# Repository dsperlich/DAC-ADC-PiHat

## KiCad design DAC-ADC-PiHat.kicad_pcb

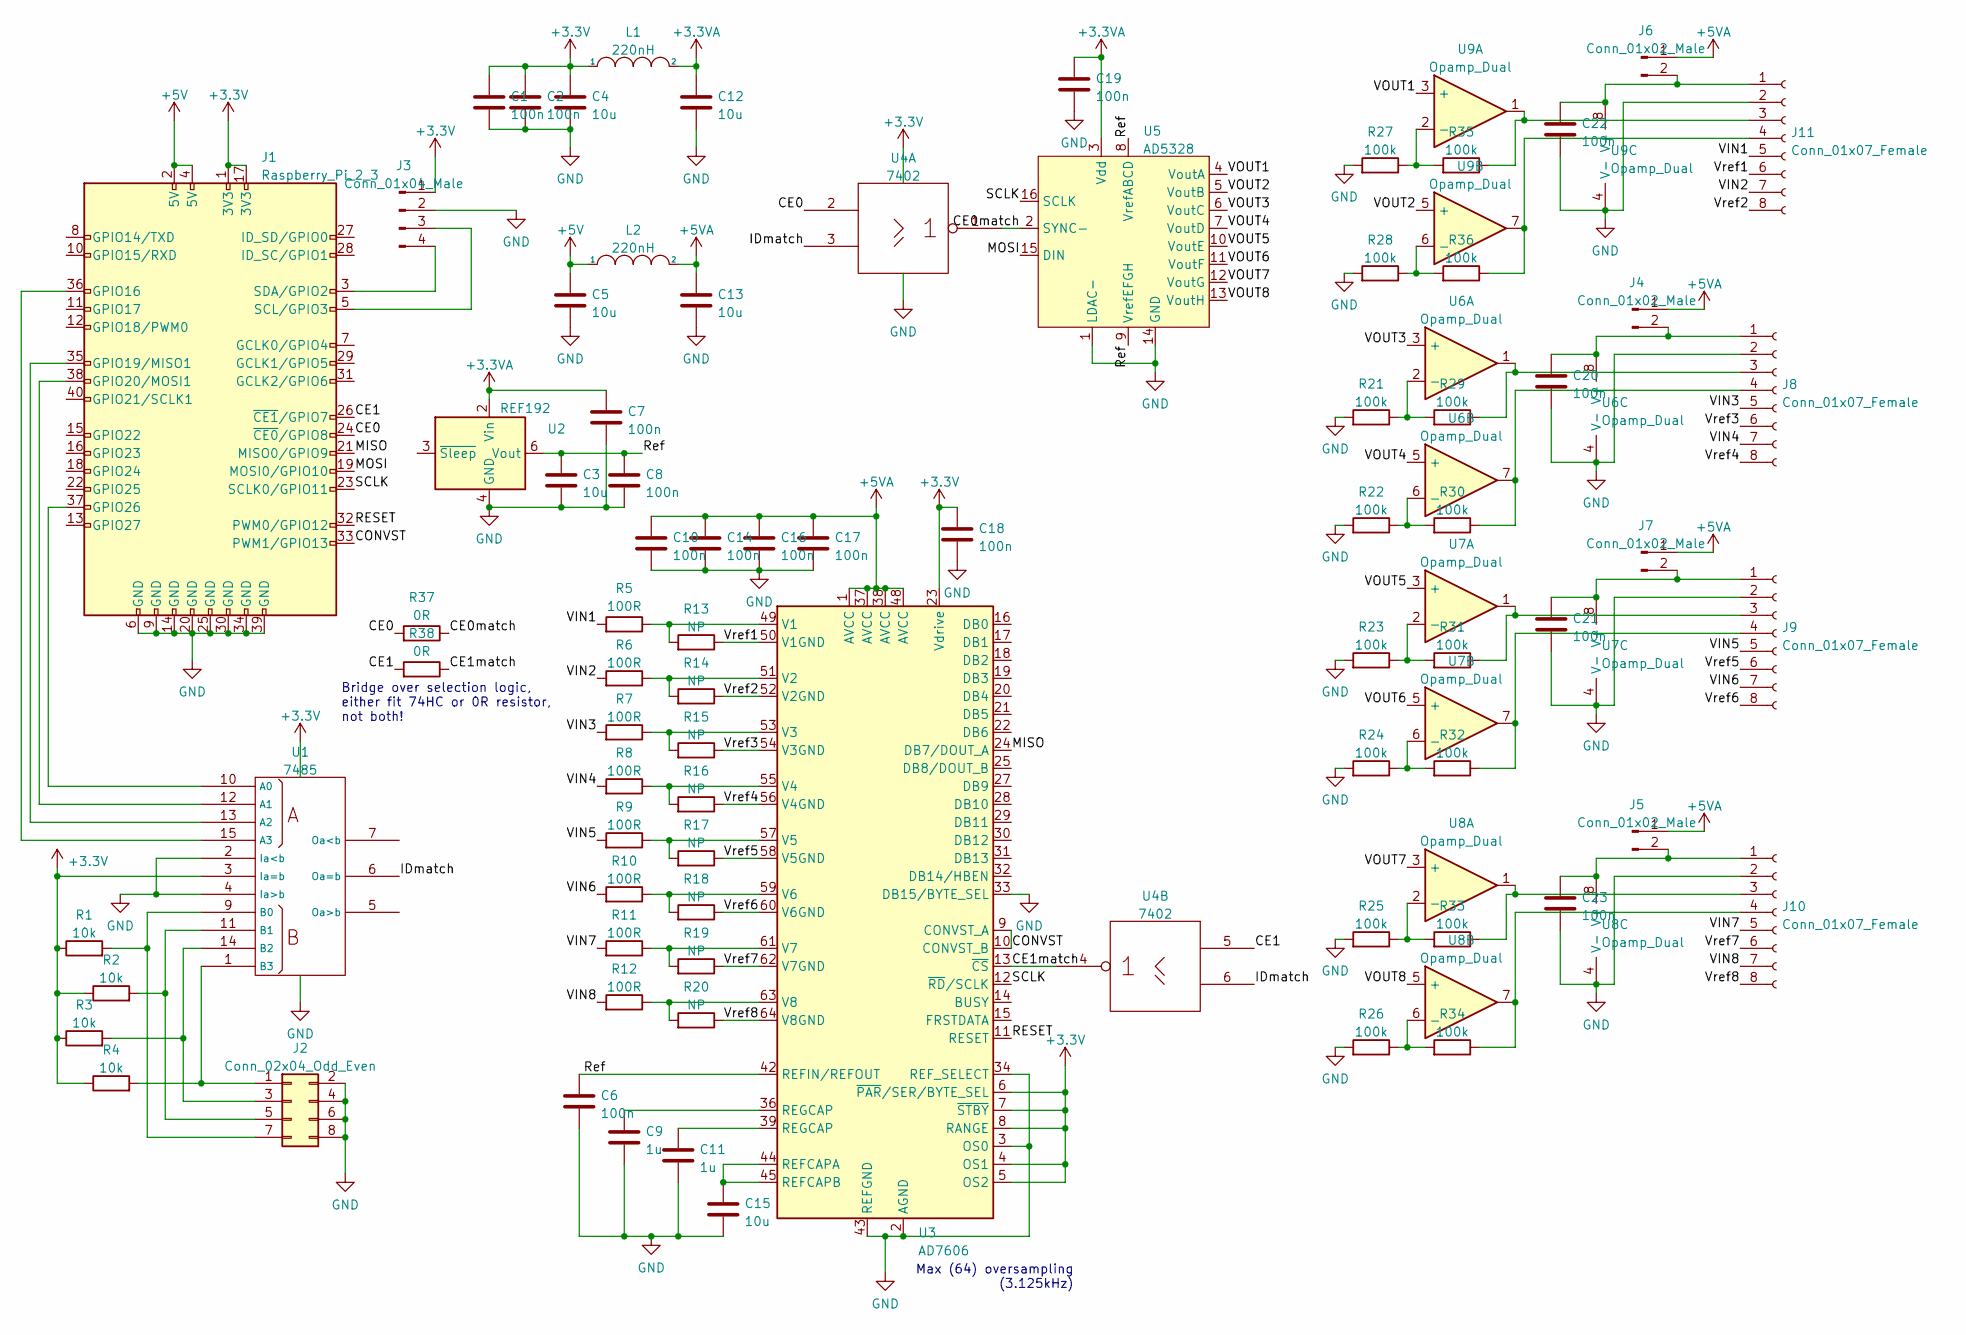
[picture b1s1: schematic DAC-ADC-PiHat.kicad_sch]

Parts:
C1, C2, C6, C7, C8, C10, C14, C16, C17, C18, C19, C20, C21, C22, C23: 100n; C_0402_1005Metric
C3, C4, C5, C12, C13, C15: 10u; C_0603_1608Metric
C9, C11: 1u; C_0603_1608Metric
J1: Raspberry_Pi_2_3; PinSocket_2x20_P2.54mm_Vertical
J2: Conn_02x04_Odd_Even; PinHeader_2x04_P2.54mm_Vertical
J3: Conn_01x04_Male; PinHeader_1x04_P2.54mm_Vertical
J4, J5, J6, J7: Conn_01x02_Male; PinHeader_1x02_P2.54mm_Vertical
J8, J9, J10, J11: Conn_01x07_Female; PinSocket_1x08_P2.54mm_Horizontal
L1, L2: 220nH; L_1210_3225Metric
R1, R2, R3, R4: 10k; R_0603_1608Metric
R5, R6, R7, R8, R9, R10, R11, R12: 100R; R_0603_1608Metric
R13, R14, R15, R16, R17, R18, R19, R20: NP; R_0603_1608Metric
R21, R22, R23, R24, R25, R26, R27, R28, R29, R30, R31, R32, R33, R34, R35, R36: 100k; R_0603_1608Metric
R37, R38: 0R; R_0603_1608Metric
U1: 7485; SOIC-16_3.9x9.9mm_P1.27mm
U2: REF192; SOIC-8_3.9x4.9mm_P1.27mm
U3: AD7606; LQFP-64_10x10mm_P0.5mm
U4: 7402; SOIC-14_3.9x8.7mm_P1.27mm
U5: AD5328; TSSOP-16-1EP_4.4x5mm_P0.65mm
U6, U7, U8, U9: Opamp_Dual; SOP-8_3.9x4.9mm_P1.27mm

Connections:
+3.3V: C1.1, C2.1, C4.1, C18.1, J1.1 (3V3), J1.17 (3V3), J3.1, L1.1, R1.1, R2.1, R3.1, R4.1, U1.3 (Ia=b), U1.16 (VCC), U3.4 (OS1), U3.5 (OS2), U3.6 (~PAR/SER/BYTE_SEL), U3.7 (~STBY), U3.8 (RANGE), U3.23 (Vdrive), U4.14 (VCC)
+3.3VA: C7.1, C12.1, C19.1, L1.2, U2.2 (Vin), U5.3 (Vdd)
+5V: C5.1, J1.2 (5V), J1.4 (5V), L2.1
+5VA: C10.1, C13.1, C14.1, C16.1, C17.1, J4.1, J5.1, J6.1, J7.1, L2.2, U3.1 (AVCC), U3.37 (AVCC), U3.38 (AVCC), U3.48 (AVCC)
/CE0: J1.24 (~CE0/GPIO8), R37.2, U4.2
/CE0match: R37.1, U4.1, U5.2 (SYNC-)
/CE1: J1.26 (~CE1/GPIO7), R38.2, U4.5
/CE1match: R38.1, U3.13 (~CS), U4.4
/CONVST: J1.33 (PWM1/GPIO13), U3.9 (CONVST_A), U3.10 (CONVST_B)
/IDmatch: U1.6 (Oa=b), U4.3, U4.6
/MISO: J1.21 (MISO0/GPIO9), U3.24 (DB7/DOUT_A)
/MOSI: J1.19 (MOSI0/GPIO10), U5.15 (DIN)
/RESET: J1.32 (PWM0/GPIO12), U3.11 (RESET)
/Ref: C3.1, C6.1, C8.1, U2.6 (Vout), U3.42 (REFIN/REFOUT), U5.8 (VrefABCD), U5.9 (VrefEFGH)
/SCLK: J1.23 (SCLK0/GPIO11), U3.12 (~RD/SCLK), U5.16 (SCLK)
/VIN1: J11.5, R5.2
/VIN2: J11.7, R6.2
/VIN3: J8.5, R7.2
/VIN4: J8.7, R8.2
/VIN5: J9.5, R9.2
/VIN6: J9.7, R10.2
/VIN7: J10.5, R11.2
/VIN8: J10.7, R12.2
/VOUT1: U5.4 (VoutA), U9.3 (+)
/VOUT2: U5.5 (VoutB), U9.5 (+)
/VOUT3: U5.6 (VoutC), U6.3 (+)
/VOUT4: U5.7 (VoutD), U6.5 (+)
/VOUT5: U5.10 (VoutE), U7.3 (+)
/VOUT6: U5.11 (VoutF), U7.5 (+)
/VOUT7: U5.12 (VoutG), U8.3 (+)
/VOUT8: U5.13 (VoutH), U8.5 (+)
/Vref1: J11.6, R13.1, U3.50 (V1GND)
/Vref2: J11.8, R14.1, U3.52 (V2GND)
/Vref3: J8.6, R15.1, U3.54 (V3GND)
/Vref4: J8.8, R16.1, U3.56 (V4GND)
/Vref5: J9.6, R17.1, U3.58 (V5GND)
/Vref6: J9.8, R18.1, U3.60 (V6GND)
/Vref7: J10.6, R19.1, U3.62 (V7GND)
/Vref8: J10.8, R20.1, U3.64 (V8GND)
GND: C1.2, C2.2, C3.2, C4.2, C5.2, C6.2, C7.2, C8.2, C9.2, C10.2, C11.2, C12.2, C13.2, C14.2, C15.2, C16.2, C17.2, C18.2, C19.2, C20.2, C21.2, C22.2, C23.2, J1.6 (GND), J1.9 (GND), J1.14 (GND), J1.20 (GND), J1.25 (GND), J1.30 (GND), J1.34 (GND), J1.39 (GND), J2.2, J2.4, J2.6, J2.8, J3.2, J8.2, J9.2, J10.2, J11.2, R21.2, R22.2, R23.2, R24.2, R25.2, R26.2, R27.2, R28.2, U1.2 (Ia<b), U1.4 (Ia>b), U1.8 (GND), U2.4 (GND), U3.2 (AGND), U3.3 (OS0), U3.26 (AGND), U3.33 (DB15/BYTE_SEL), U3.34 (REF_SELECT), U3.35 (AGND), U3.40 (AGND), U3.41 (AGND), U3.43 (REFGND), U3.46 (REFGND), U3.47 (AGND), U4.7 (GND), U5.1 (LDAC-), U5.14 (GND), U6.4 (V-), U7.4 (V-), U8.4 (V-), U9.4 (V-)
unnamed: C9.1, U3.36 (REGCAP)
unnamed: C11.1, U3.39 (REGCAP)
unnamed: C15.1, U3.44 (REFCAPA), U3.45 (REFCAPB)
unnamed: C22.1, J6.2, J11.1, U9.8 (V+)
unnamed: C23.1, J5.2, J10.1, U8.8 (V+)
unnamed: J1.3 (SDA/GPIO2), J3.4
unnamed: J1.5 (SCL/GPIO3), J3.3
unnamed: J1.35 (GPIO19/MISO1), U1.13 (A2)
unnamed: J1.36 (GPIO16), U1.15 (A3)
unnamed: J1.37 (GPIO26), U1.10 (A0)
unnamed: J2.1, R4.2, U1.1 (B3)
unnamed: J2.3, R3.2, U1.14 (B2)
unnamed: J2.5, R2.2, U1.11 (B1)
unnamed: J2.7, R1.2, U1.9 (B0)
unnamed: C20.1, J4.2, J8.1, U6.8 (V+)
unnamed: C21.1, J7.2, J9.1, U7.8 (V+)
unnamed: J8.3, R29.1, U6.1
unnamed: J8.4, R30.1, U6.7
unnamed: J9.3, R31.1, U7.1
unnamed: J9.4, R32.1, U7.7
unnamed: J10.3, R33.1, U8.1
unnamed: J10.4, R34.1, U8.7
unnamed: J11.3, R35.1, U9.1
unnamed: J11.4, R36.1, U9.7
unnamed: R10.1, R18.2, U3.59 (V6)
unnamed: R11.1, R19.2, U3.61 (V7)
unnamed: R12.1, R20.2, U3.63 (V8)
unnamed: R5.1, R13.2, U3.49 (V1)
unnamed: R6.1, R14.2, U3.51 (V2)
unnamed: R7.1, R15.2, U3.53 (V3)
unnamed: R8.1, R16.2, U3.55 (V4)
unnamed: R9.1, R17.2, U3.57 (V5)
unnamed: R21.1, R29.2, U6.2 (-)
unnamed: R22.1, R30.2, U6.6 (-)
unnamed: R23.1, R31.2, U7.2 (-)
unnamed: R24.1, R32.2, U7.6 (-)
unnamed: R25.1, R33.2, U8.2 (-)
unnamed: R26.1, R34.2, U8.6 (-)
unnamed: R27.1, R35.2, U9.2 (-)
unnamed: R28.1, R36.2, U9.6 (-)
unnamed: J1.38 (GPIO20/MOSI1), U1.12 (A1)

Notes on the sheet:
Max (64) oversampling (3.125kHz)
Bridge over selection logic, either fit 74HC or 0R resistor, not both!

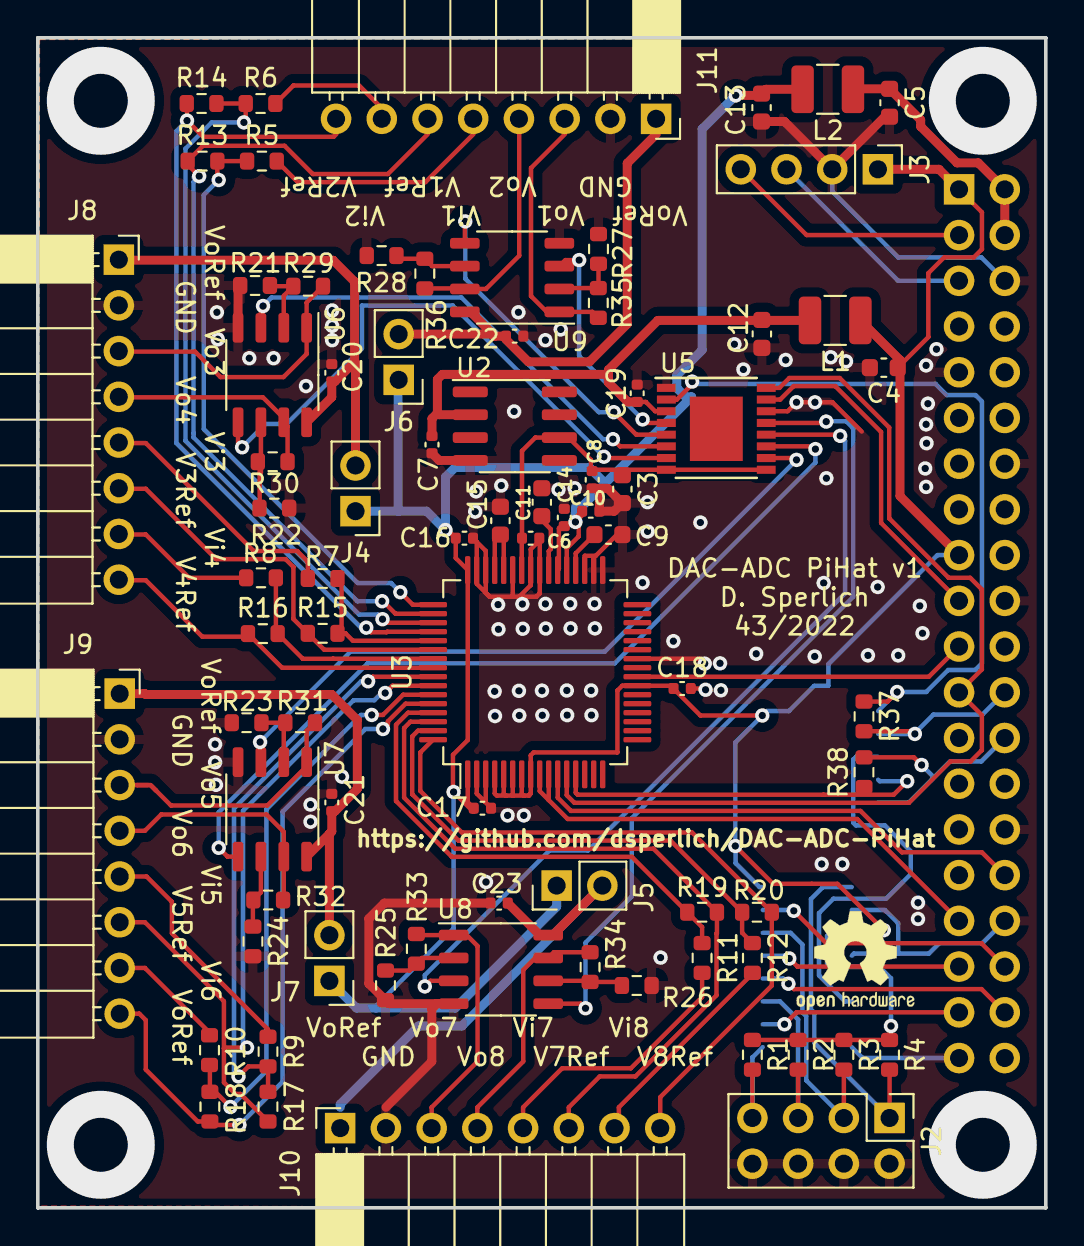
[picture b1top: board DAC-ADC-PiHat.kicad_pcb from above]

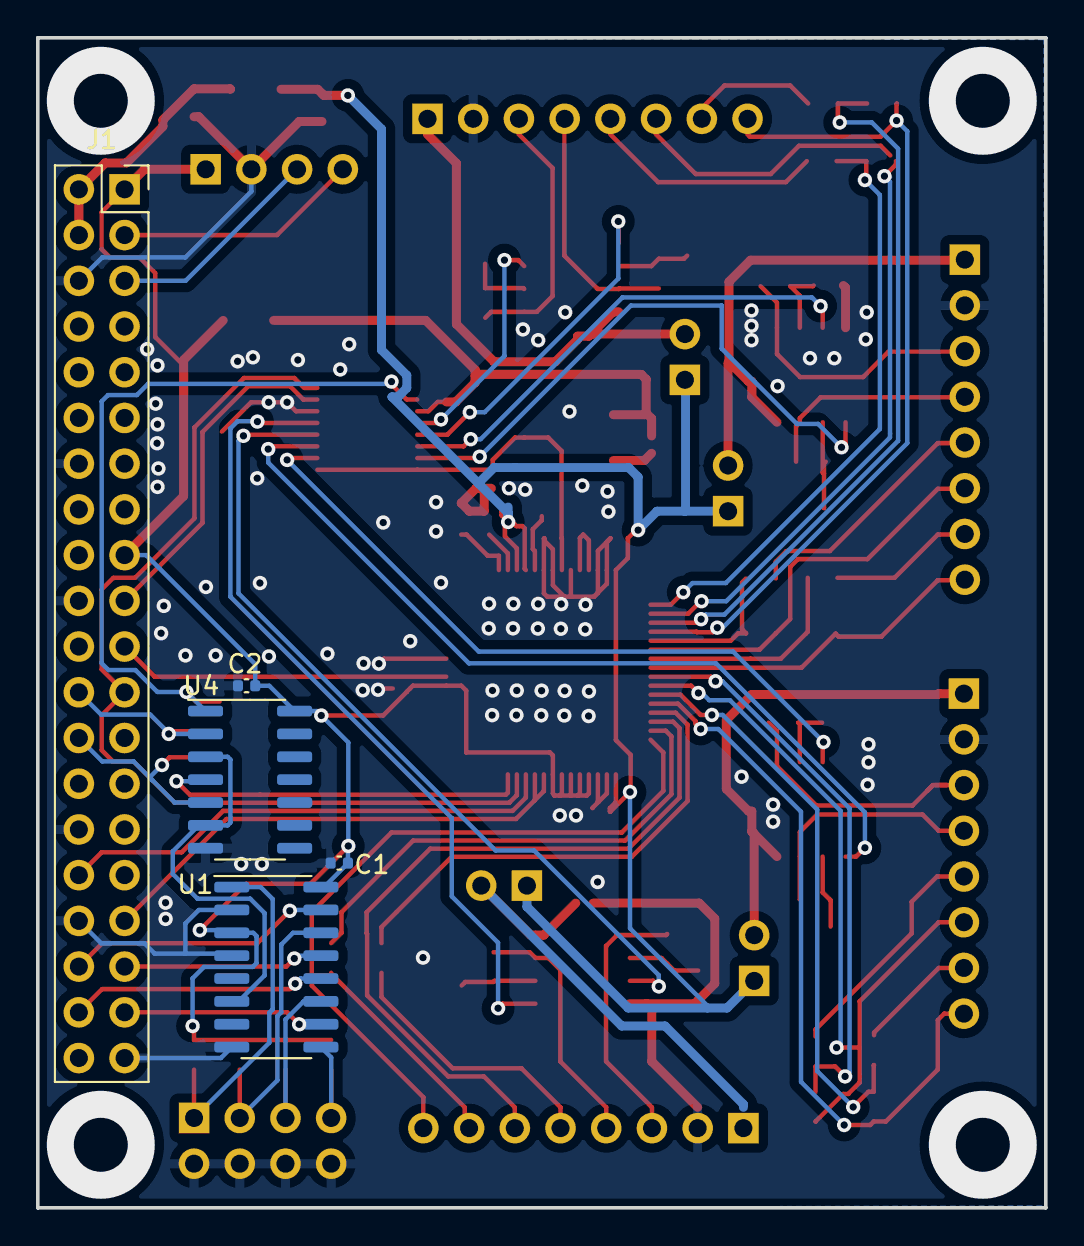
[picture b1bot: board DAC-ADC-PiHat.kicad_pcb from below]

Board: 2 copper layers, 56.0 x 65.0 mm, 83 parts (5 on the bottom side), 81 nets.

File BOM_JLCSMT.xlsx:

Comment | Designator | Footprint | JLCPCB Part #（optional）
Conn_01x08_Female | J11,J10,J9,J8 | PinSocket_1x08_P2.54mm_Horizontal
0R | R38,R37 | R_0603_1608Metric | C21189
100k | R36,R35,R34,R33,R32,R31,R30,R29,R28,R27,R26,R25,R24,R23,R22,R21 | R_0603_1608Metric | C22936
NP | R20,R19,R18,R17,R16,R15,R14,R13 | R_0603_1608Metric
100R | R12,R11,R10,R9,R8,R7,R6,R5 | R_0603_1608Metric | C22775
100n | C23,C22,C21,C20,C19,C18,C17,C16,C14,C10,C8,C7,C6,C2,C1 | C_0402_1005Metric | C307331
Raspberry_Pi_2_3 | J1 | PinSocket_2x20_P2.54mm_Vertical
Opamp_Dual | U9,U8,U7,U6 | SOP-8_3.9x4.9mm_P1.27mm | C2685362
AD5328 | U5 | TSSOP-16-1EP_4.4x5mm_P0.65mm | C29162
74HC02 | U4 | SOIC-14_3.9x8.7mm_P1.27mm | C5588
AD7606 | U3 | LQFP-64_10x10mm_P0.5mm | C16725
REF192 | U2 | SOIC-8_3.9x4.9mm_P1.27mm | C27314
74HC85 | U1 | SOIC-16_3.9x9.9mm_P1.27mm | C5953
10k | R4,R2,R3,R1 | R_0603_1608Metric | C25804
INDUCTOR | L2,L1 | L_1210_3225Metric | C295225
Conn_01x02_Male | J7,J6,J5,J4 | PinHeader_1x02_P2.54mm_Vertical | C2905434
Conn_01x04_Male | J3 | PinHeader_1x04_P2.54mm_Vertical | C2905435
Conn_02x04_Odd_Even | J2 | PinHeader_2x04_P2.54mm_Vertical | C225519
10u | C15,C13,C12,C5,C4,C3 | C_0603_1608Metric | C96446
1u | C11,C9 | C_0603_1608Metric | C15849
